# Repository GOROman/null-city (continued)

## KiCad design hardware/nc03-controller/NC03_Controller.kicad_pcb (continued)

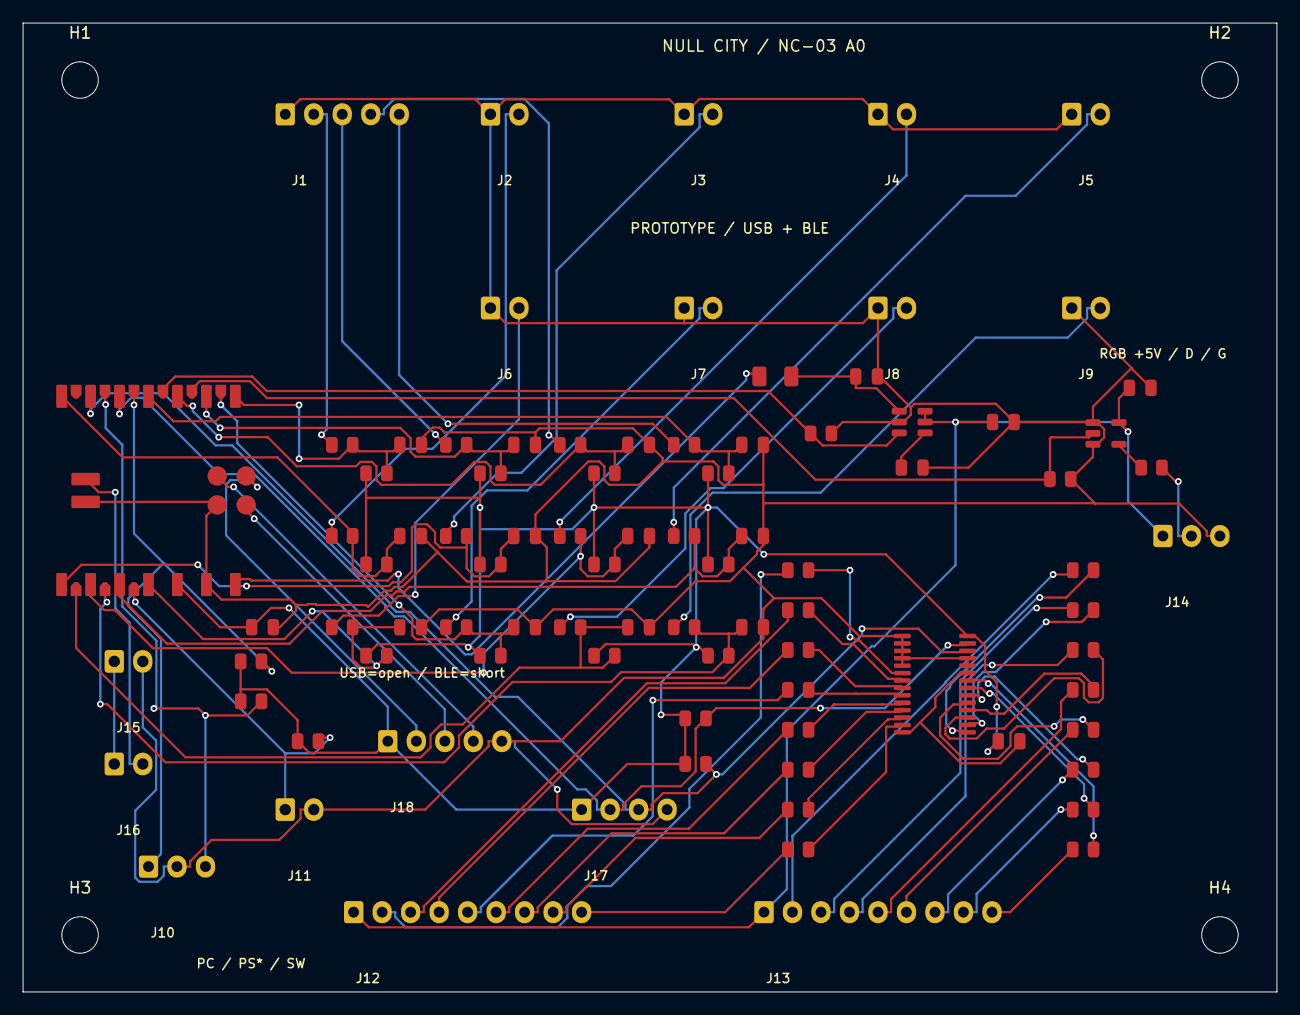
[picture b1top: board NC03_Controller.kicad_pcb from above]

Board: 2 copper layers, 110.0 x 85.0 mm, 93 parts (0 on the bottom side), 76 nets.

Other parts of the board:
H1, H2, H3, H4: MountingHole_3.2mm_M3

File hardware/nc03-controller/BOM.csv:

Reference,Value,Footprint,Datasheet
U1,XIAO nRF52840 Plus,NC03:XIAO_nRF52840_Plus,https://wiki.seeedstudio.com/XIAO_BLE/
J1,LEVER: G U D L R,NC03:Connector_JST_JST_XH_B5B-XH-A_1x05_P2.50mm_Vertical,
J2,B1: G SIG,NC03:Connector_JST_JST_XH_B2B-XH-A_1x02_P2.50mm_Vertical,
J3,B2: G SIG,NC03:Connector_JST_JST_XH_B2B-XH-A_1x02_P2.50mm_Vertical,
J4,B3: G SIG,NC03:Connector_JST_JST_XH_B2B-XH-A_1x02_P2.50mm_Vertical,
J5,B4: G SIG,NC03:Connector_JST_JST_XH_B2B-XH-A_1x02_P2.50mm_Vertical,
J6,B5: G SIG,NC03:Connector_JST_JST_XH_B2B-XH-A_1x02_P2.50mm_Vertical,
J7,B6: G SIG,NC03:Connector_JST_JST_XH_B2B-XH-A_1x02_P2.50mm_Vertical,
J8,1P: G SIG,NC03:Connector_JST_JST_XH_B2B-XH-A_1x02_P2.50mm_Vertical,
J9,START: G SIG,NC03:Connector_JST_JST_XH_B2B-XH-A_1x02_P2.50mm_Vertical,
R1,330,NC03:Resistor_SMD_R_0805_2012Metric,
R21,10k,NC03:Resistor_SMD_R_0805_2012Metric,
C1,1nF,NC03:Capacitor_SMD_C_0805_2012Metric,
R2,330,NC03:Resistor_SMD_R_0805_2012Metric,
R22,10k,NC03:Resistor_SMD_R_0805_2012Metric,
C2,1nF,NC03:Capacitor_SMD_C_0805_2012Metric,
R3,330,NC03:Resistor_SMD_R_0805_2012Metric,
R23,10k,NC03:Resistor_SMD_R_0805_2012Metric,
C3,1nF,NC03:Capacitor_SMD_C_0805_2012Metric,
R4,330,NC03:Resistor_SMD_R_0805_2012Metric,
R24,10k,NC03:Resistor_SMD_R_0805_2012Metric,
C4,1nF,NC03:Capacitor_SMD_C_0805_2012Metric,
R5,330,NC03:Resistor_SMD_R_0805_2012Metric,
R25,10k,NC03:Resistor_SMD_R_0805_2012Metric,
C5,1nF,NC03:Capacitor_SMD_C_0805_2012Metric,
R6,330,NC03:Resistor_SMD_R_0805_2012Metric,
R26,10k,NC03:Resistor_SMD_R_0805_2012Metric,
C6,1nF,NC03:Capacitor_SMD_C_0805_2012Metric,
R7,330,NC03:Resistor_SMD_R_0805_2012Metric,
R27,10k,NC03:Resistor_SMD_R_0805_2012Metric,
C7,1nF,NC03:Capacitor_SMD_C_0805_2012Metric,
R8,330,NC03:Resistor_SMD_R_0805_2012Metric,
R28,10k,NC03:Resistor_SMD_R_0805_2012Metric,
C8,1nF,NC03:Capacitor_SMD_C_0805_2012Metric,
R9,330,NC03:Resistor_SMD_R_0805_2012Metric,
R29,10k,NC03:Resistor_SMD_R_0805_2012Metric,
C9,1nF,NC03:Capacitor_SMD_C_0805_2012Metric,
R10,330,NC03:Resistor_SMD_R_0805_2012Metric,
R30,10k,NC03:Resistor_SMD_R_0805_2012Metric,
C10,1nF,NC03:Capacitor_SMD_C_0805_2012Metric,
R11,330,NC03:Resistor_SMD_R_0805_2012Metric,
R31,10k,NC03:Resistor_SMD_R_0805_2012Metric,
C11,1nF,NC03:Capacitor_SMD_C_0805_2012Metric,
R12,330,NC03:Resistor_SMD_R_0805_2012Metric,
R32,10k,NC03:Resistor_SMD_R_0805_2012Metric,
C12,1nF,NC03:Capacitor_SMD_C_0805_2012Metric,
U2,PCA9685PW,NC03:Package_SO_TSSOP-28_4.4x9.7mm_P0.65mm,https://www.nxp.com/docs/en/data-sheet/PCA9685.pdf
R41,1k,NC03:Resistor_SMD_R_0805_2012Metric,
R42,1k,NC03:Resistor_SMD_R_0805_2012Metric,
R43,1k,NC03:Resistor_SMD_R_0805_2012Metric,
R44,1k,NC03:Resistor_SMD_R_0805_2012Metric,
R45,1k,NC03:Resistor_SMD_R_0805_2012Metric,
R46,1k,NC03:Resistor_SMD_R_0805_2012Metric,
R47,1k,NC03:Resistor_SMD_R_0805_2012Metric,
R48,1k,NC03:Resistor_SMD_R_0805_2012Metric,
R49,1k,NC03:Resistor_SMD_R_0805_2012Metric,
R50,1k,NC03:Resistor_SMD_R_0805_2012Metric,
R51,1k,NC03:Resistor_SMD_R_0805_2012Metric,
R52,1k,NC03:Resistor_SMD_R_0805_2012Metric,
R53,1k,NC03:Resistor_SMD_R_0805_2012Metric,
R54,1k,NC03:Resistor_SMD_R_0805_2012Metric,
R55,1k,NC03:Resistor_SMD_R_0805_2012Metric,
R56,1k,NC03:Resistor_SMD_R_0805_2012Metric,
J12,DIR LEDs: +5 K0..K7,NC03:Connector_JST_JST_XH_B9B-XH-A_1x09_P2.50mm_Vertical,
J13,BTN LEDs: +5 K8..K15,NC03:Connector_JST_JST_XH_B9B-XH-A_1x09_P2.50mm_Vertical,
F1,350mA PTC,NC03:Fuse_Fuse_1206_3216Metric,
U3,TPS22918DBVR,NC03:Package_TO_SOT_SMD_SOT-23-6,https://www.ti.com/lit/ds/symlink/tps22918.pdf
R60,100k,NC03:Resistor_SMD_R_0805_2012Metric,
C20,10nF,NC03:Capacitor_SMD_C_0805_2012Metric,
C21,1uF,NC03:Capacitor_SMD_C_0805_2012Metric,
C22,47uF 10V,NC03:Capacitor_SMD_C_0805_2012Metric,
U4,SN74LV1T125DBVR,NC03:Package_TO_SOT_SMD_SOT-23-5,https://www.ti.com/lit/ds/symlink/sn74lv1t125.pdf
R61,330,NC03:Resistor_SMD_R_0805_2012Metric,
R62,100k,NC03:Resistor_SMD_R_0805_2012Metric,
J14,RGB: +5 DIN GND,NC03:Connector_JST_JST_XH_B3B-XH-A_1x03_P2.50mm_Vertical,
C23,100nF,NC03:Capacitor_SMD_C_0805_2012Metric,
C24,100nF,NC03:Capacitor_SMD_C_0805_2012Metric,
C25,1uF,NC03:Capacitor_SMD_C_0805_2012Metric,
R63,4.7k,NC03:Resistor_SMD_R_0805_2012Metric,
R64,4.7k,NC03:Resistor_SMD_R_0805_2012Metric,
J10,MODE: PC G SW,NC03:Connector_JST_JST_XH_B3B-XH-A_1x03_P2.50mm_Vertical,
J11,LINK: USB=open BLE=short,NC03:Connector_JST_JST_XH_B2B-XH-A_1x02_P2.50mm_Vertical,
R65,10k,NC03:Resistor_SMD_R_0805_2012Metric,
R66,10k,NC03:Resistor_SMD_R_0805_2012Metric,
R67,10k,NC03:Resistor_SMD_R_0805_2012Metric,
J15,BATTERY: + GND,NC03:Connector_JST_JST_XH_B2B-XH-A_1x02_P2.50mm_Vertical,
J16,BAT SWITCH: IN OUT,NC03:Connector_JST_JST_XH_B2B-XH-A_1x02_P2.50mm_Vertical,
J17,AUX: 3V3 SDA SCL G,NC03:Connector_JST_JST_XH_B4B-XH-A_1x04_P2.50mm_Vertical,
J18,SWD: 3V3 IO CLK RST G,NC03:Connector_JST_JST_XH_B5B-XH-A_1x05_P2.50mm_Vertical,
